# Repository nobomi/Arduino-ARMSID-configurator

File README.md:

# Arduino ARMSID configurator

Simple Arduino shield with a sketch for ARMSID and ARM2SID configuration using Tera Term or similar ANSI terminal program. It allows:

- configure ARMSID or ARM2SID parameters (SID type, address mappings, filters, digifix, ...)
- update ARMSID or ARM2SID firmware
- play some SIDs to a 3.5 mm stereo audio jack (more than 60 ohms headphones or line input connection only)

&nbsp;&nbsp;&nbsp;&nbsp;&nbsp;&nbsp;

#### ANSI terminal (Tera Term) configuration screen samples

&nbsp;&nbsp;&nbsp;&nbsp;

&nbsp;&nbsp;&nbsp;&nbsp;

### Schematic and PCB Layout

[Schematic](PCB/Arduino_AMRSID_tester_dual_sch.pdf)

[PCB Layout - Gerber files](PCB/Gerber/Arduino_AMRSID_tester_dual_Gerber.zip)

### Connectors

#### ARM2SID

Main DIL28 socket for ARMSID or ARM2SID to be configured.

#### SID2

DIL28 socket for the 2nd ARMSID or SID2 (ARM2SID). When using SID2, please use 6-pin PicoBlade connector with 5 cm wire to connect SID2 to ARM2SID.  

#### AUDIO1

Stereo audio output for headphones or amplifier line input.

Pin | Description     
--- | ---------------
Tip (the inner outer contact) | Output: Audio left (>60 ohms or line level)
Second row (the inner middle contact) | Output: Audio right (>60 ohms or line level)
Ring / Sleeve         |	Ground (GND)

Note: When connecting headphones, the impedance should be at least 60 ohm.
Note2: Shorten the connector legs near the board edge to not exceed the hole before soldering. Solder without creating solder (tin) bump, clean and cover with Kapton tape, as it could conflict with Arduino USB connector otherwise.

#### SOCKET (53047-06)

6-pin MOLEX PicoBlade connector for ARM2SID 2nd SID connection. Use 10 cm 6-pin PicoBlade connectors wire to ARM2SID instead of populating SID2 socket. 

Pin | Description     
--- | ---------------
1 | GND
2 | GND
3 |	Output: R/W (R/W signal for the 2nd socket)
4 |	Output: CS2 (CS signal for the 2nd socket)
5 | GND
6 | Input: Audio right

#### Arduino

Arduino pin headers used to connect to Arduino UNO. Only models with ATmega328P should be used, such as **Arduino UNO Rev3** or **Arduino UNO Rev3 SMD**.

### Bill of Materials

Component type | Reference         | Description                                | Quantity | Possible sources           | Notes
-------------- | ----------------- | ------------------------------------------ | -------- | -------------------------- | --------
PCB            |                   | Arduino ARMSID configurator shield PCB     | 1        | Order PCB or parts kit at [Retrocomp.cz e-shop](https://www.retrocomp.cz) or order from a PCB manufacturer of your choice using provided Gerber or Eagle files |  
Resistor       | R1, R2, R3, R4    | 110 kohm, SMD 0805                         | 4        | Digikey [RMCF0805FT110KCT-ND](https://www.digikey.com/product-detail/en/stackpole-electronics-inc/RMCF0805FT110K/RMCF0805FT110KCT-ND/2418241) | Needed only if you want to test POT inputs  
Capacitor      | C1, C2            | 100 nF, SMD 0805                           | 2        | Digikey [490-11955-1-ND](https://www.digikey.com/product-detail/en/murata-electronics/GCD21BR71H104KA01L/490-11955-1-ND/5403192) |  
Capacitor      | C3, C4, C5, C6    | 2.2 nF, SMD 0805                           | 4        | Digikey [490-6448-1-ND](https://www.digikey.com/product-detail/en/murata-electronics/GRM2165C2A222JA01D/490-6448-1-ND/3845645) | Needed only if you want to test POT inputs  
Capacitor      | C7, C8            | 10 uF, SMD 3528                            | 2        | Digikey [478-4975-1-ND](https://www.digikey.com/product-detail/en/avx-corporation/TPSB106M016R0800/478-4975-1-ND/1888186)      | Needed only if you want to use stereo audio output     
Capacitor      | C9, C10, C11, C12 | 15 nF, SMD 0805                            | 4        | Digikey [490-5718-1-ND](https://www.digikey.com/product-detail/en/murata-electronics/GR321AD72E153KW01D/490-5718-1-ND/2712261) | Needed only if you plan to use real SIDs (no sufficient power provided for real SIDs on current design)  
DIP/DIL Socket | ARM2SID, SID2     | 28 pin DIL socket (preferably ZIF)         | 2        | Digikey [3M2802-ND](https://www.digikey.cz/product-detail/cs/3m/228-1277-00-0602J/3M2802-ND/95268) or [A302-ND](https://www.digikey.cz/product-detail/cs/aries-electronics/28-6554-10/A302-ND/27592)  | The second (SID2) DIL socket si needed only for the ARM2SID's 2nd SID configuration and can be substitued by 10 cm 6-pin PicoBlade wire to the SOCKET connector.
Connector      | AUDIO1            | Audio connector JACK 3.5 mm - type FC68125 | 1        | Farnell [2309468](https://cz.farnell.com/cliff-electronic-components/fc68125/connector-phono-3-5mm-jack-4pole/dp/2309468)      | Needed only if you want to use stereo audio output  
Connector      | SOCKET            | Molex PicoBlade 6-pin vertical header      | 1        | Digikey [WM1735-ND](https://www.digikey.com/product-detail/en/molex/0530470610/WM1735-ND/242857)                               | Needed only if you want connect ARM2SID to board without SID2  
Connector      | B1                | Arduino stackable header kit               | 1        | Digikey [1568-1413-ND](https://www.digikey.com/product-detail/en/sparkfun-electronics/PRT-11417/1568-1413-ND/6161755)          |  
Arduino        | B1                | Arduino UNO Rev3                           | 1        | Digikey [1050-1041-ND](https://www.digikey.com/product-detail/end/arduino/A000073/1050-1041-ND/3476357) or [1050-1024-ND](https://www.digikey.com/product-detail/en/arduino/A000066/1050-1024-ND/2784006) |   

## Known Issues
* Version 1.0
  * 3.5 mm audio JACK touches the Arduino USB connector. Solder without tin bump and isolate with Kapton tape!
  * No power supply for real SIDs. The 5V provided is not sufficient for MOS 6581 nor 8580.  

## Guide
DARRELL A. WESTBURY created nice guide for configuring and updating ARMSID/ARM2SID using Arduino shield [GET IT HERE](https://docs.google.com/document/d/1B_xzXlLjq3NbKnOrhIoJ5PrlVIhlsD_aASEhB0CWK90/edit?usp=sharing). He also shared his experience with setup and using ARM2SID in MB6582. Thank you!

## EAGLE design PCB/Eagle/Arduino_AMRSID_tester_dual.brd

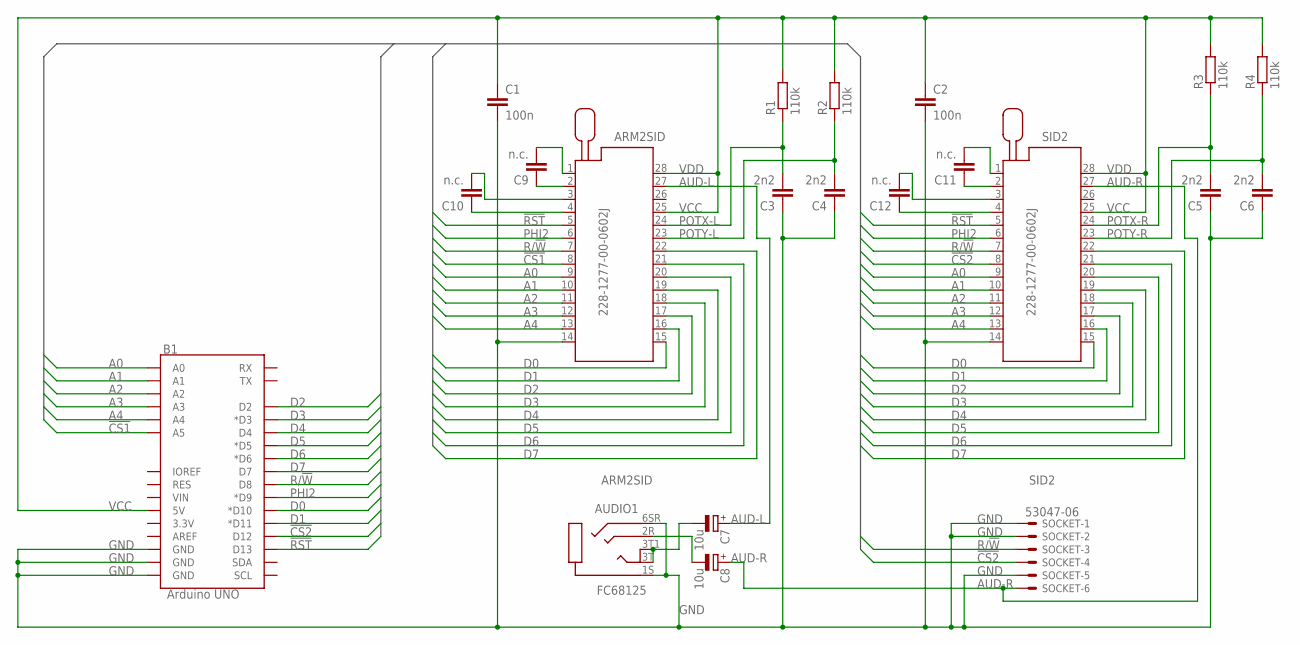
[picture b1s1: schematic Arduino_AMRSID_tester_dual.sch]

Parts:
ARM2SID: 228-1277-00-0602J
AUDIO1: FC68125
B1: Arduino UNO; UNO_R3_SHIELD
C1, C2: 100n; C0805K
C3, C4, C5, C6: 2n2; C0805K
C7, C8: 10u; B/3528-21R
C9, C10, C11, C12: n.c.; C0805K
R1, R2, R3, R4: 110k; R0805
SID2: 228-1277-00-0602J
SOCKET: 53047-06

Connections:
!CS1: ARM2SID.8, B1.A5
!CS2: B1.D12, SID2.8, SOCKET.4
!RST: ARM2SID.5, B1.D13, SID2.5
A0: ARM2SID.9, B1.A0, SID2.9
A1: ARM2SID.10, B1.A1, SID2.10
A2: ARM2SID.11, B1.A2, SID2.11
A3: ARM2SID.12, B1.A3, SID2.12
A4: ARM2SID.13, B1.A4, SID2.13
AUD-L: ARM2SID.27, C7.+
AUD-R: C8.+, SID2.27, SOCKET.6
D0: ARM2SID.15, B1.D10 (*D10), SID2.15
D1: ARM2SID.16, B1.D11 (*D11), SID2.16
D2: ARM2SID.17, B1.D2, SID2.17
D3: ARM2SID.18, B1.D3 (*D3), SID2.18
D4: ARM2SID.19, B1.D4, SID2.19
D5: ARM2SID.20, B1.D5 (*D5), SID2.20
D6: ARM2SID.21, B1.D6 (*D6), SID2.21
D7: ARM2SID.22, B1.D7, SID2.22
GND: ARM2SID.14, AUDIO1.1S, AUDIO1.6SR, B1.GND@0 (GND), B1.GND@1 (GND), B1.GND@2 (GND), C1.2, C2.2, C3.1, C4.1, C5.1, C6.1, SID2.14, SOCKET.1, SOCKET.2, SOCKET.5
unnamed: AUDIO1.2R, C8.-
unnamed: ARM2SID.2, C9.1
unnamed: AUDIO1.3T, AUDIO1.3T1, C7.-
unnamed: ARM2SID.1, C9.2
unnamed: C11.1, SID2.2
unnamed: C11.2, SID2.1
unnamed: ARM2SID.4, C10.1
unnamed: ARM2SID.3, C10.2
unnamed: C12.1, SID2.4
unnamed: C12.2, SID2.3
PHI2: ARM2SID.6, B1.D9 (*D9), SID2.6
POTX-L: ARM2SID.24, C3.2, R1.1
POTX-R: C5.2, R3.1, SID2.24
POTY-L: ARM2SID.23, C4.2, R2.1
POTY-R: C6.2, R4.1, SID2.23
R/!W: ARM2SID.7, B1.D8, SID2.7, SOCKET.3
VCC: ARM2SID.25, ARM2SID.28, B1.5V, C1.1, C2.1, R1.2, R2.2, R3.2, R4.2, SID2.25, SID2.28

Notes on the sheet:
ARM2SID
SID2
VDD

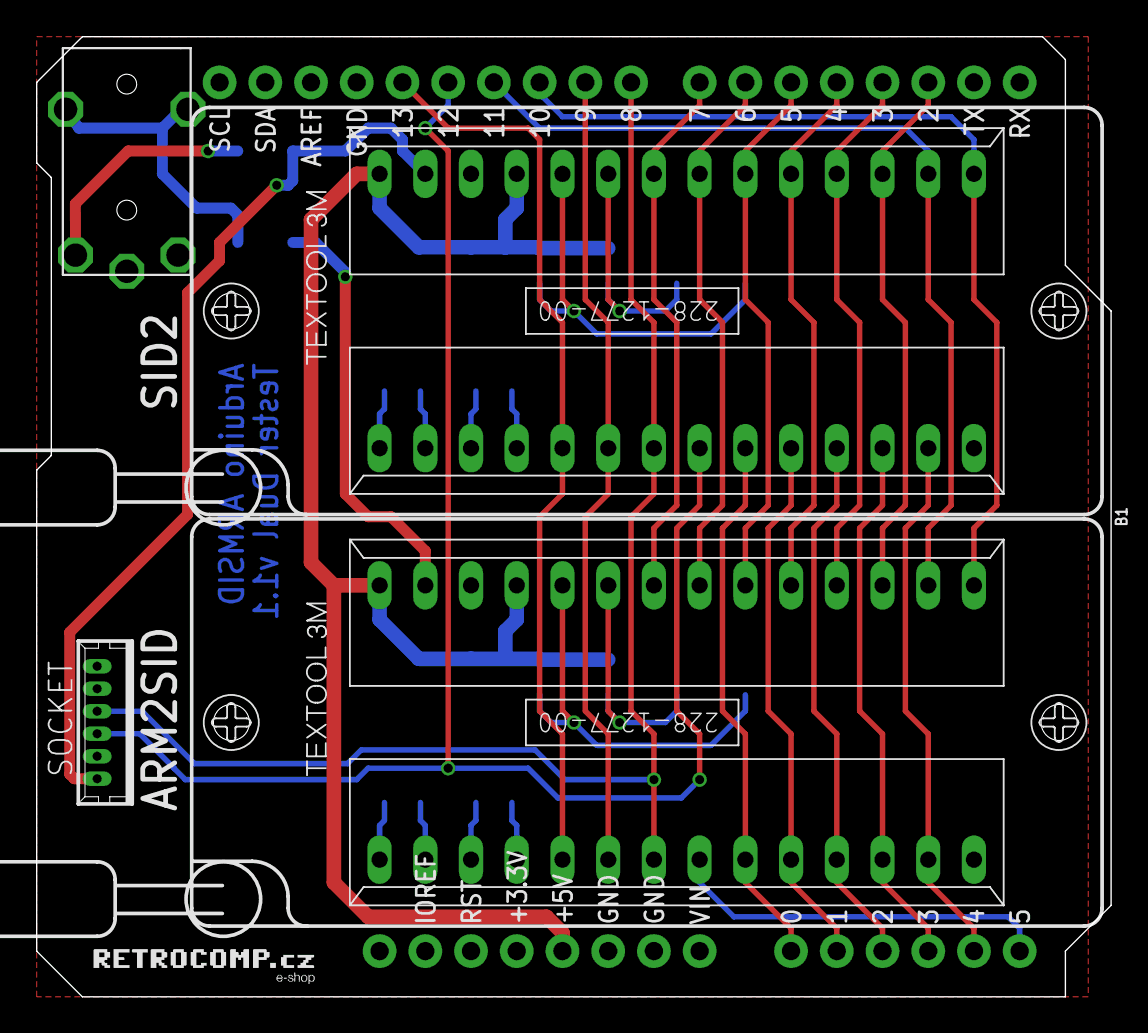
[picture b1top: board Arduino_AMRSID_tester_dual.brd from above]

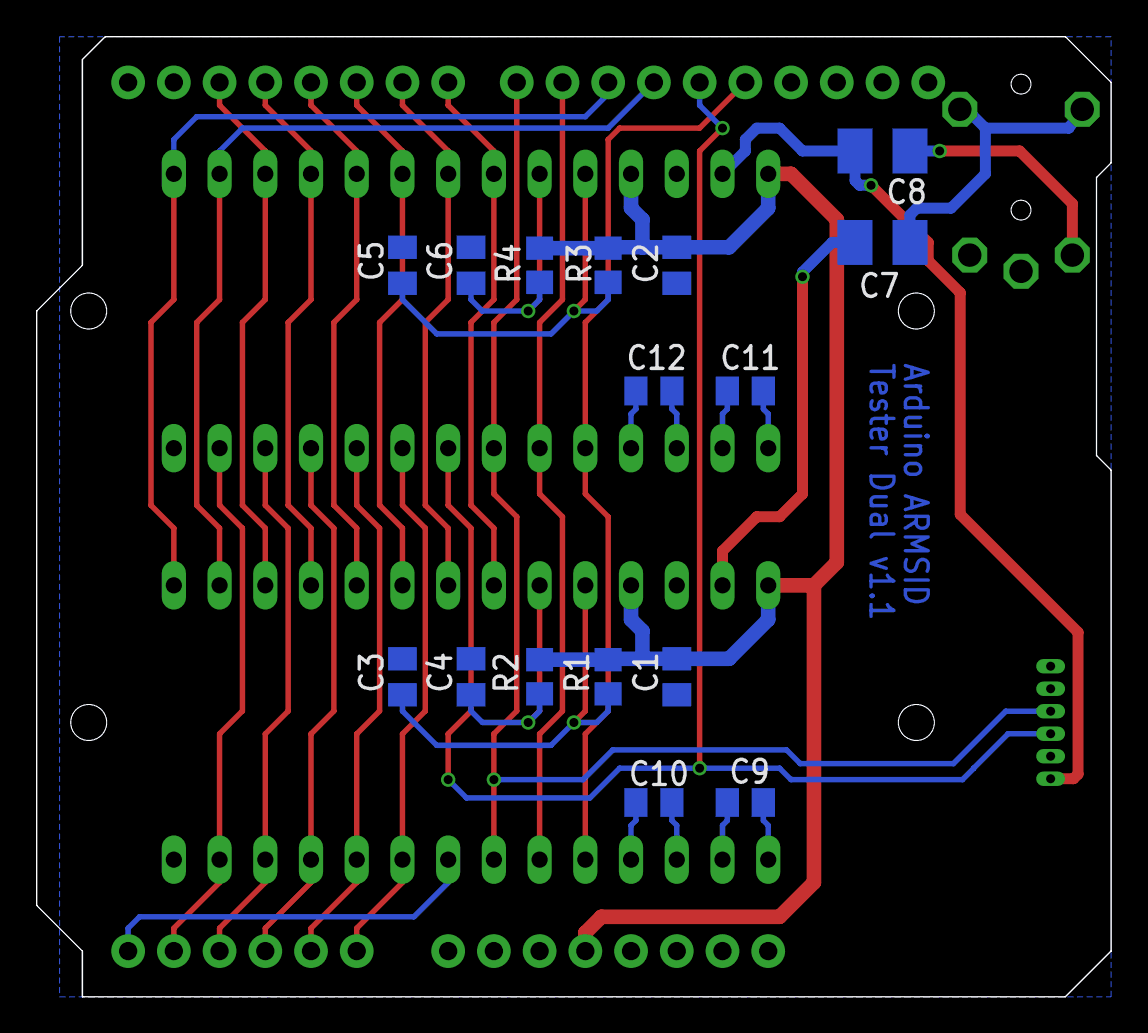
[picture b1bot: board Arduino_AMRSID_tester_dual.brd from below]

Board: 4 copper layers, 59.7 x 53.3 mm, 21 parts (16 on the bottom side), 36 nets.

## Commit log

2021-04-08 Create LICENSE
2021-04-08 ARMSID FW updater
2021-04-09 Folder structure reorganization
2021-04-09 .gitignore added
2021-04-09 Copyright updated - MIT License
2021-04-11 Schematic update for better readability
2021-04-11 Readme updated, images added
2021-04-17 faster io, terminal init
2021-04-17 SCH and PCB update
2021-04-17 Schematic and PCB cleanup, v1.1 Gerbers
2021-08-25 SIDplay410 demo video added
2021-08-27 SIDplay ported macOS/unix/linux (termios.h)
2021-08-27 SIDplay: aim for 10us sleep after write() (macOS/unix)
    Without this, the sample Hexadecimal_2SID.sid would play 99% good, but
    stall for a second a few times during the track. And setting it to 100us
    caused the track to play too slow. 10us seems to work nicely.
2021-12-06 Test 2.13
2022-08-04 ARMSID Tester updated for ARMSID fw 2.14 and ARM2SID fw 3.14
2022-08-04 latest firmware zipped and put into 'firmware_for_Arduino_updater' folder
2022-08-04 firmware info txt file added
2022-08-08 Added link do Darrell's MB6582 guide
2023-01-16 ARMSID firmware update 2.15
2023-03-03 FW 3.15 for ARM2SID
2023-03-03 configurator/tester version update 2.15 and 3.15
2023-03-07 cputs2 with variable string fix
2024-06-15 ARMSID fw 2.16 compatibility
2024-06-15 ARMSID fw 2.16 compatibility - added switch to enable EXT IN - added switch to lower autodetection values for SID type
2024-06-22 ARMSID FW 2.16 for updater
2024-06-25 old fw2.15 removed
2026-03-03 firmware update - binary 2.17 for ARMSID and 3.17 for ARM2SID

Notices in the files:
parts and their libraries:
SparkFun-Boards: Licensing: Creative Commons ShareAlike 4.0 International - https://creativecommons.org/licenses/by-sa/4.0
